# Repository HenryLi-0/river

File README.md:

<div align="center">
    <h2>River</h2>
    <p>by <a href= "https://github.com/HenryLi-0/river"> @HenryLi-0 </a></p>
    
</div>

<sub>All designs are open source! Hardware licensed under CERN OHL S v2.<sub>

# River

a quick stepping stone

---

## What this?

A couple of months ago, after listening to [archived](https://archive.org/details/the-sport-saver?webamp=default) [music](https://archive.org/details/under-the-ground?webamp=default) on the Internet Archive with Webamp, I thought the graphics on the right side (powered by Milkdrop) were pretty cool. I've always liked how Geometry Dash levels *typically* have well synced gameplay, since it's just so satisfying. Additionally, I also dislike how everything is switching to streamsing services (both because of the subscription model and more importantly the amount of cellular data it uses lol), so I basically wanted to bring music-synced graphics onto a portable offline device!

So, River is a relatively small PCB, hosting a dual RP2040 setup, each having custom firmware! The first one handles all the user controls, file loading, and the audio jack, while the second handles the display math, communicating with the first RP2040 by SPI and UART. Through this (rather unconventional) setup, audio can play continously while the second RP2040 works on more taxing graphics using the Pico SDK for C, with the second RP2040 basically just doing the graphics. It does this by having a PCM5101A and a TPA6132A2RTE into a TRS audio jack!

In retrospect, this project wasn't exactly a quick stepping stone (as in, it took over fifty hours of development), but it sure did review many topics surrounding PCB design with KiCAD, building on to what I learned from Hackpad and Raven! Originally, this was in case [fermion](http://github.com/HenryLi-0/fermion) would require a custom PCB, but who knows if it'll need one in the end. Anyways, working on River did teach a lot, as well as letting me have fun creating art for it!

---

Huge thanks to [this](https://blueprint.hackclub.com/starter-projects/devboard) guide from Blueprint and [this](https://pip-assets.raspberrypi.com/categories/814-rp2040/documents/RP-008279-DS-1-hardware-design-with-rp2040.pdf) documentation from Raspberry Pi for valuable information on RP2040 wiring design. Thanks!

---

## Pictures!

---

## Directory

- [CAD](</cad/README.md>)
    - The case is made in Onshape!
- [Firmware](</firmware/README.md>)
    - Two firmwares for the two RP2040s!
- [Updatelogs](</updatelogs/>)
    - As always, lots of behind the scenes content! It's also a decently long read as always :D
- [BOM](</BOM.csv>)
    - Want to build one yourself? Here's the BOM in CSV form! However, I suggest using the Google Sheets one, check down below for that!

---

## Usage

Assembly
1. First, one must obtain the PCB! It's not really made for hand-soldering, more so for JLCPCB's or any other PCBA service to assemble (but feel free to give it a try if super experienced!).
2. The main PCB's here? Great! Flash the two RP2040s with their specific firmwares and make sure all status LEDs and storage works! (Same process as testing a devboard, except there's not really any free pins...)
3. Once the RP2040s are confirmed to be in good condition, test the micro SD card slot and the audio jack! A micro SD card and a TRS audio plug (usually in random earbuds) are needed! Load music on and see if it works (after setting the firmware to play a song from the micro SD card).
4. Once those also work, solder on the displays and keys! This should be fairly straightforward, watch a soldering tutorial if needed! (Yes, a soldering iron is also needed!)
5. Assemble everything into the case and screw in the M2 screws! Adjust the case if needed if the audio plug doesn't fit well with the current slot!

---

## BOM

Note: This list was made in mid-September 2026. Depending on a ton of factors, this price may change over time, so these prices may be different! Multiple parts are sourced by me (since I have a bunch of extra parts laying around), so it will likely cost a bit more. Currently, shipping and tax estimates are included (to NYC), check out the `updatelogs` whenever construction occurs to find the actual price it resulted in!

[Here's](https://docs.google.com/spreadsheets/d/1_4eaDKRTe7VvPdyKRilJCp6rfzp3SGLLEaJtn6RHo0M/edit?gid=0#gid=0) the original Google Sheets BOM, color coded too! (It'll also be more updated, but I'll try to sync this one too!)

| Part                                      | Price         | Link          |
|-------------------------------------------|---------------|---------------|
| Board PCB (PCBA)                          | $84.61        | JLCPCB        |
| M2 Screws (16mm, 50pcs)                   | $1.41         | [AliExpress](https://www.aliexpress.us/item/3256804341271555.html) |
| 128x32 OLED Display (White, 1pc)          | $2.44         | [AliExpress](https://www.aliexpress.us/item/3256808453793642.html) |
| 128x160 TFT Display (1.8 inch TFT)        | $4.06         | [AliExpress](https://www.aliexpress.us/item/3256807859088652.html) |
| WS2812B LEDs (3)                          | $0.00         | Anywhere      |
| Micro SD Card (1)                         | $0.00         | Anywhere      |
| EC11 Rotary Encoder (1)                   | $0.00         | Anywhere      |
| Cherry MX Switch (3)                      | $0.00         | Anywhere      |
| Estimated Shipping (JLCPCB to NYC)        | $11.05        | JLCPCB        |
| Estimated Shipping (AliExpress to NYC)    | $0.00         | AliExpress    |
| Buffer                                    | $5.00         |               |
| TOTAL                                     | $108.57       |               |

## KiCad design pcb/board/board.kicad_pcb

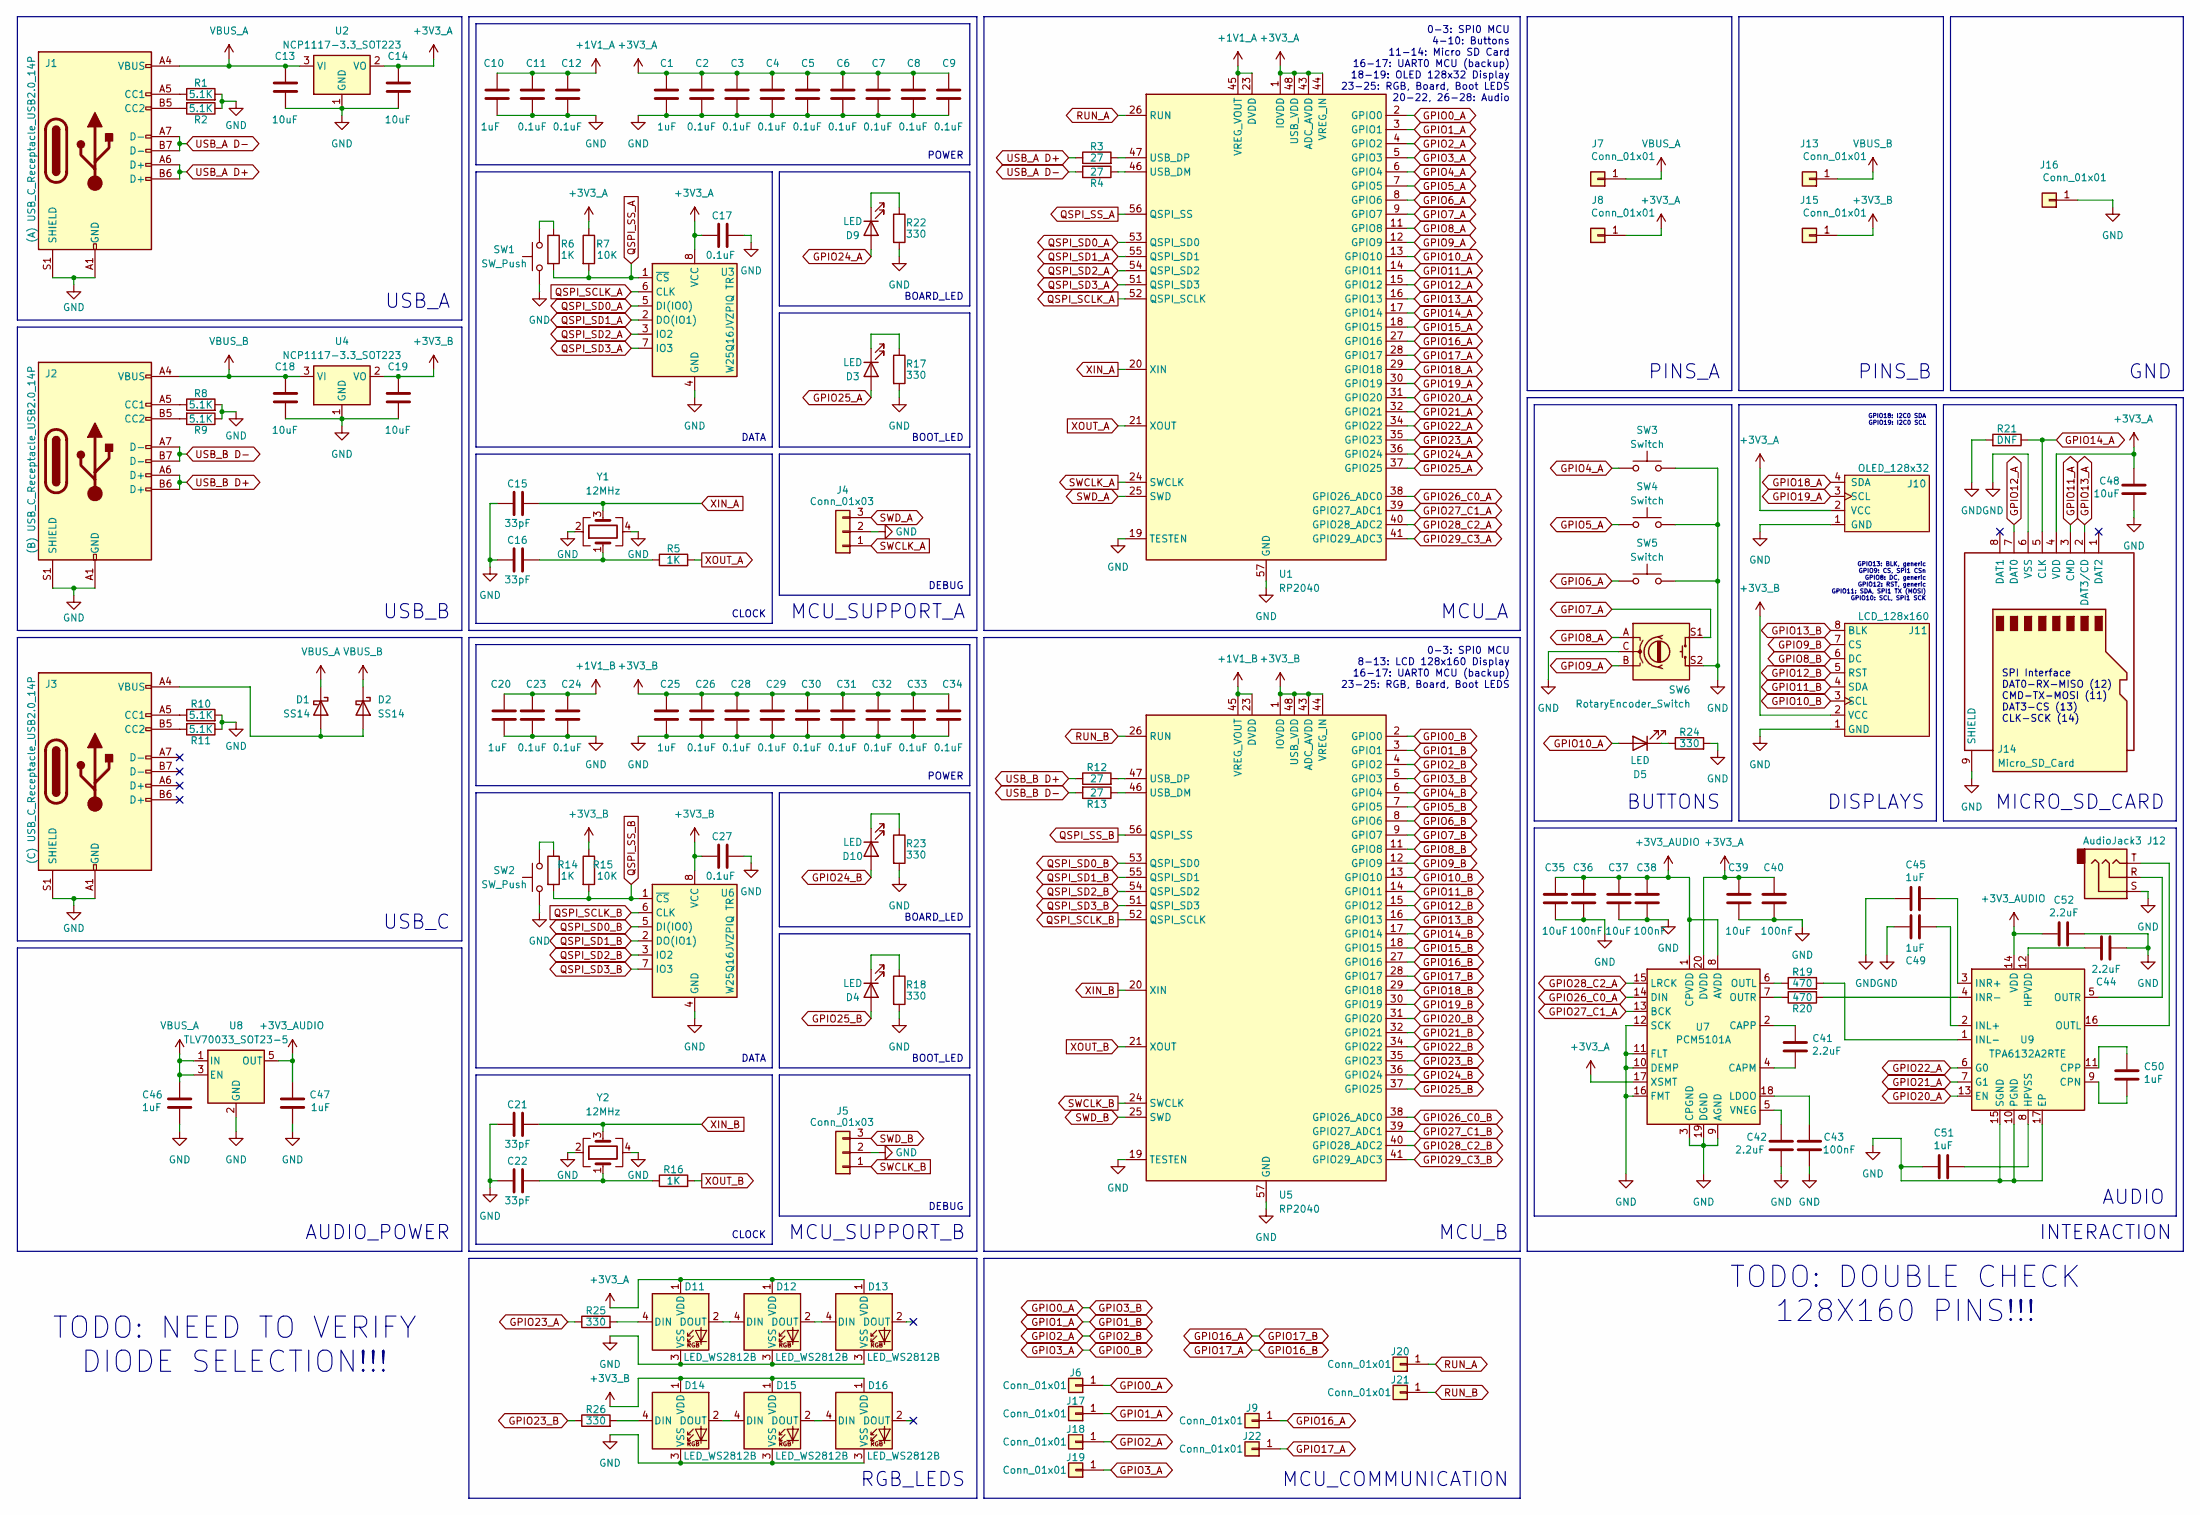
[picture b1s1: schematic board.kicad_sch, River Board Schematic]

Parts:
C1, C10, C20, C25, C45, C46, C47, C49, C50, C51: 1uF; C_0402_1005Metric
C2, C3, C4, C5, C6, C7, C8, C9, C11, C12, C17, C23, C24, C26, C27, C28, C29, C30, C31, C32, C33, C34: 0.1uF; C_0402_1005Metric
C13, C14, C18, C19: 10uF; C_0603_1608Metric
C15, C16, C21, C22: 33pF; C_0402_1005Metric
C35, C37, C39, C48: 10uF; C_0402_1005Metric
C36, C38, C40, C43: 100nF; C_0402_1005Metric
C41, C42, C44, C52: 2.2uF; C_0402_1005Metric
D1, D2: SS14; D_SMA
D3, D4, D5, D9, D10: LED; LED_0603_1608Metric
D11, D12, D13, D14, D15, D16: LED_WS2812B
J1: (A) USB_C_Receptacle_USB2.0_14P; USB_C_Receptacle_HRO_TYPE-C-31-M-12
J2: (B) USB_C_Receptacle_USB2.0_14P; USB_C_Receptacle_HRO_TYPE-C-31-M-12
J3: (C) USB_C_Receptacle_USB2.0_14P; USB_C_Receptacle_HRO_TYPE-C-31-M-12
J4, J5: Conn_01x03; PinHeader_1x03_P2.54mm_Vertical
J6, J9, J17, J18, J19, J20, J21, J22: Conn_01x01; TestPoint_Pad_D1.0mm
J7, J13: Conn_01x01; TestPoint_Pad_1.0x1.0mm
J8, J15, J16: Conn_01x01; PinHeader_1x01_P2.54mm_Vertical
J10: OLED_128x32
J11: LCD_128x160
J12: AudioJack3; Jack_3.5mm_CUI_SJ-3523-SMT_Horizontal
J14: Micro_SD_Card; microSD_HC_Molex_47219-2001
R1, R2, R8, R9, R10, R11: 5.1K; R_0402_1005Metric
R3, R4, R12, R13: 27; R_0402_1005Metric
R5, R6, R14, R16: 1K; R_0402_1005Metric
R7, R15: 10K; R_0402_1005Metric
R17, R18, R22, R23, R24, R25, R26: 330; R_0402_1005Metric
R19, R20: 470; R_0402_1005Metric
R21: DNF; R_0402_1005Metric
SW1, SW2: SW_Push; SW_Push_SPST_NO_Alps_SKRK
SW3, SW4, SW5: Switch; SW_Cherry_MX_1.00u_PCB
SW6: RotaryEncoder_Switch; RotaryEncoder_Alps_EC11E-Switch_Vertical_H20mm
U1, U5: RP2040; QFN-56-1EP_7x7mm_P0.4mm_EP3.2x3.2mm
U2, U4: NCP1117-3.3_SOT223; SOT-223-3_TabPin2
U3, U6: W25Q16JVZPIQ TR; Winbond_USON-8-1EP_3x2mm_P0.5mm_EP0.2x1.6mm
U7: PCM5101A; TSSOP-20_4.4x6.5mm_P0.65mm
U8: TLV70033_SOT23-5; SOT-23-5
U9: TPA6132A2RTE; WQFN-16-1EP_3x3mm_P0.5mm_EP1.6x1.6mm_ThermalVias
Y1, Y2: 12MHz; Crystal_SMD_3225-4Pin_3.2x2.5mm

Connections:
+1V1_A: C10.1, C11.1, C12.1, U1.23 (DVDD), U1.45 (VREG_VOUT), U1.50 (DVDD)
+1V1_B: C20.1, C23.1, C24.1, U5.23 (DVDD), U5.45 (VREG_VOUT), U5.50 (DVDD)
+3V3_A: C1.1, C2.1, C3.1, C4.1, C5.1, C6.1, C7.1, C8.1, C9.1, C14.1, C17.1, C39.1, C40.1, C48.1, D11.1 (VDD), D12.1 (VDD), D13.1 (VDD), J8.1, J10.2 (VCC), J14.4 (VDD), R7.1, U1.1 (IOVDD), U1.10 (IOVDD), U1.22 (IOVDD), U1.33 (IOVDD), U1.42 (IOVDD), U1.43 (ADC_AVDD), U1.44 (VREG_IN), U1.48 (USB_VDD), U1.49 (IOVDD), U2.2 (VO), U3.8 (VCC), U7.17 (XSMT), U7.20 (DVDD)
+3V3_AUDIO: C35.1, C36.1, C37.1, C38.1, C47.1, C52.1, U7.1 (CPVDD), U7.8 (AVDD), U8.5 (OUT), U9.14 (VDD)
+3V3_B: C19.1, C25.1, C26.1, C27.1, C28.1, C29.1, C30.1, C31.1, C32.1, C33.1, C34.1, D14.1 (VDD), D15.1 (VDD), D16.1 (VDD), J11.2 (VCC), J15.1, R15.1, U4.2 (VO), U5.1 (IOVDD), U5.10 (IOVDD), U5.22 (IOVDD), U5.33 (IOVDD), U5.42 (IOVDD), U5.43 (ADC_AVDD), U5.44 (VREG_IN), U5.48 (USB_VDD), U5.49 (IOVDD), U6.8 (VCC)
GND: C1.2, C2.2, C3.2, C4.2, C5.2, C6.2, C7.2, C8.2, C9.2, C10.2, C11.2, C12.2, C13.2, C14.2, C15.1, C16.1, C17.2, C18.2, C19.2, C20.2, C21.1, C22.1, C23.2, C24.2, C25.2, C26.2, C27.2, C28.2, C29.2, C30.2, C31.2, C32.2, C33.2, C34.2, C35.2, C36.2, C37.2, C38.2, C39.2, C40.2, C42.2, C43.2, C44.2, C45.1, C46.2, C47.2, C48.2, C49.1, C51.1, C52.2, D11.3 (VSS), D12.3 (VSS), D13.3 (VSS), D14.3 (VSS), D15.3 (VSS), D16.3 (VSS), J1.A1 (GND), J1.A12 (GND), J1.B1 (GND), J1.B12 (GND), J1.S1 (SHIELD), J2.A1 (GND), J2.A12 (GND), J2.B1 (GND), J2.B12 (GND), J2.S1 (SHIELD), J3.A1 (GND), J3.A12 (GND), J3.B1 (GND), J3.B12 (GND), J3.S1 (SHIELD), J4.2, J5.2, J10.1 (GND), J11.1 (GND), J12.S, J14.6 (VSS), J14.9 (SHIELD), J16.1, R1.2, R2.1, R8.2, R9.1, R10.2, R11.1, R17.2, R18.2, R21.2, R22.2, R23.2, R24.2, SW1.1, SW2.1, SW3.2, SW4.2, SW5.2, SW6.C, SW6.S2, U1.19 (TESTEN), U1.57 (GND), U2.1 (GND), U3.4 (GND), U4.1 (GND), U5.19 (TESTEN), U5.57 (GND), U6.4 (GND), U7.3 (CPGND), U7.9 (AGND), U7.10 (DEMP), U7.11 (FLT), U7.12 (SCK), U7.16 (FMT), U7.19 (DGND), U8.2 (GND), U9.10 (PGND), U9.15 (SGND), U9.17 (EP), Y1.2, Y1.4, Y2.2, Y2.4
GPIO0_A: J6.1, U1.2 (GPIO0), U5.5 (GPIO3)
GPIO0_B: J19.1, U1.5 (GPIO3), U5.2 (GPIO0)
GPIO1_A: J17.1, U1.3 (GPIO1), U5.3 (GPIO1)
GPIO2_A: J18.1, U1.4 (GPIO2), U5.4 (GPIO2)
GPIO4_A: SW3.1, U1.6 (GPIO4)
GPIO4_B: U5.6 (GPIO4)
GPIO5_A: SW4.1, U1.7 (GPIO5)
GPIO5_B: U5.7 (GPIO5)
GPIO6_A: SW5.1, U1.8 (GPIO6)
GPIO6_B: U5.8 (GPIO6)
GPIO7_A: SW6.S1, U1.9 (GPIO7)
GPIO7_B: U5.9 (GPIO7)
GPIO8_A: SW6.A, U1.11 (GPIO8)
GPIO8_B: J11.6 (DC), U5.11 (GPIO8)
GPIO9_A: SW6.B, U1.12 (GPIO9)
GPIO9_B: J11.7 (CS), U5.12 (GPIO9)
GPIO10_A: D5.2 (A), U1.13 (GPIO10)
GPIO10_B: J11.3 (SCL), U5.13 (GPIO10)
GPIO11_A: J14.3 (CMD), U1.14 (GPIO11)
GPIO11_B: J11.4 (SDA), U5.14 (GPIO11)
GPIO12_A: J14.7 (DAT0), U1.15 (GPIO12)
GPIO12_B: J11.5 (RST), U5.15 (GPIO12)
GPIO13_A: J14.2 (DAT3/CD), U1.16 (GPIO13)
GPIO13_B: J11.8 (BLK), U5.16 (GPIO13)
GPIO14_A: J14.5 (CLK), R21.1, U1.17 (GPIO14)
GPIO14_B: U5.17 (GPIO14)
GPIO15_A: U1.18 (GPIO15)
GPIO15_B: U5.18 (GPIO15)
GPIO16_A: J9.1, U1.27 (GPIO16), U5.28 (GPIO17)
GPIO16_B: J22.1, U1.28 (GPIO17), U5.27 (GPIO16)
GPIO18_A: J10.4 (SDA), U1.29 (GPIO18)
GPIO18_B: U5.29 (GPIO18)
GPIO19_A: J10.3 (SCL), U1.30 (GPIO19)
GPIO19_B: U5.30 (GPIO19)
GPIO20_A: U1.31 (GPIO20), U9.13 (EN)
GPIO20_B: U5.31 (GPIO20)
GPIO21_A: U1.32 (GPIO21), U9.7 (G1)
GPIO21_B: U5.32 (GPIO21)
GPIO22_A: U1.34 (GPIO22), U9.6 (G0)
GPIO22_B: U5.34 (GPIO22)
GPIO23_A: R25.1, U1.35 (GPIO23)
GPIO23_B: R26.1, U5.35 (GPIO23)
GPIO24_A: D9.2 (A), U1.36 (GPIO24)
GPIO24_B: D10.2 (A), U5.36 (GPIO24)
GPIO25_A: D3.2 (A), U1.37 (GPIO25)
GPIO25_B: D4.2 (A), U5.37 (GPIO25)
GPIO26_C0_A: U1.38 (GPIO26_ADC0), U7.14 (DIN)
GPIO26_C0_B: U5.38 (GPIO26_ADC0)
GPIO27_C1_A: U1.39 (GPIO27_ADC1), U7.13 (BCK)
GPIO27_C1_B: U5.39 (GPIO27_ADC1)
GPIO28_C2_A: U1.40 (GPIO28_ADC2), U7.15 (LRCK)
GPIO28_C2_B: U5.40 (GPIO28_ADC2)
GPIO29_C3_A: U1.41 (GPIO29_ADC3)
GPIO29_C3_B: U5.41 (GPIO29_ADC3)
unnamed: C16.2, R5.1, Y1.1
unnamed: C22.2, R16.1, Y2.1
unnamed: D1.2 (A), D2.2 (A), J3.A4 (VBUS), J3.A9 (VBUS), J3.B4 (VBUS), J3.B9 (VBUS)
unnamed: D3.1 (K), R17.1
unnamed: D4.1 (K), R18.1
unnamed: D5.1 (K), R24.1
unnamed: D9.1 (K), R22.1
unnamed: D10.1 (K), R23.1
unnamed: D11.4 (DIN), R25.2
unnamed: D11.2 (DOUT), D12.4 (DIN)
unnamed: D12.2 (DOUT), D13.4 (DIN)
unnamed: D14.4 (DIN), R26.2
unnamed: D14.2 (DOUT), D15.4 (DIN)
unnamed: D15.2 (DOUT), D16.4 (DIN)
unnamed: J1.A5 (CC1), R1.1
unnamed: J1.B5 (CC2), R2.2
unnamed: J2.A5 (CC1), R8.1
unnamed: J2.B5 (CC2), R9.2
unnamed: J3.A5 (CC1), R10.1
unnamed: J3.B5 (CC2), R11.2
unnamed: R6.1, SW1.2
unnamed: R14.1, SW2.2
unnamed: R4.1, U1.46 (USB_DM)
unnamed: R3.2, U1.47 (USB_DP)
unnamed: R13.1, U5.46 (USB_DM)
unnamed: R12.2, U5.47 (USB_DP)
unnamed: C41.2, U7.4 (CAPM)
unnamed: C41.1, U7.2 (CAPP)
unnamed: C43.1, U7.18 (LDOO)
unnamed: R19.1, U7.6 (OUTL)
unnamed: R20.1, U7.7 (OUTR)
unnamed: C42.1, U7.5 (VNEG)
unnamed: C50.2, U9.9 (CPN)
unnamed: C50.1, U9.11 (CPP)
unnamed: C44.1, U9.12 (HPVDD)
unnamed: C51.2, U9.8 (HPVSS)
unnamed: C49.2, U9.2 (INL+)
unnamed: R19.2, U9.1 (INL-)
unnamed: C45.2, U9.3 (INR+)
unnamed: R20.2, U9.4 (INR-)
unnamed: J12.T, U9.16 (OUTL)
unnamed: J12.R, U9.5 (OUTR)
QSPI_SCLK_A: U1.52 (QSPI_SCLK), U3.6 (CLK)
QSPI_SCLK_B: U5.52 (QSPI_SCLK), U6.6 (CLK)
QSPI_SD0_A: U1.53 (QSPI_SD0), U3.5 (DI(IO0))
QSPI_SD0_B: U5.53 (QSPI_SD0), U6.5 (DI(IO0))
QSPI_SD1_A: U1.55 (QSPI_SD1), U3.2 (DO(IO1))
QSPI_SD1_B: U5.55 (QSPI_SD1), U6.2 (DO(IO1))
QSPI_SD2_A: U1.54 (QSPI_SD2), U3.3 (IO2)
QSPI_SD2_B: U5.54 (QSPI_SD2), U6.3 (IO2)
QSPI_SD3_A: U1.51 (QSPI_SD3), U3.7 (IO3)
QSPI_SD3_B: U5.51 (QSPI_SD3), U6.7 (IO3)
QSPI_SS_A: R6.2, R7.2, U1.56 (QSPI_SS), U3.1 (~CS)
QSPI_SS_B: R14.2, R15.2, U5.56 (QSPI_SS), U6.1 (~CS)
RUN_A: J20.1, U1.26 (RUN)
RUN_B: J21.1, U5.26 (RUN)
SWCLK_A: J4.1, U1.24 (SWCLK)
SWCLK_B: J5.1, U5.24 (SWCLK)
SWD_A: J4.3, U1.25 (SWD)
SWD_B: J5.3, U5.25 (SWD)
USB_A D+: J1.A6 (D+), J1.B6 (D+), R3.1
USB_A D-: J1.A7 (D-), J1.B7 (D-), R4.2
USB_B D+: J2.A6 (D+), J2.B6 (D+), R12.1
USB_B D-: J2.A7 (D-), J2.B7 (D-), R13.2
VBUS_A: C13.1, C46.1, D1.1 (K), J1.A4 (VBUS), J1.A9 (VBUS), J1.B4 (VBUS), J1.B9 (VBUS), J7.1, U2.3 (VI), U8.1 (IN), U8.3 (EN)
VBUS_B: C18.1, D2.1 (K), J2.A4 (VBUS), J2.A9 (VBUS), J2.B4 (VBUS), J2.B9 (VBUS), J13.1, U4.3 (VI)
XIN_A: C15.2, U1.20 (XIN), Y1.3
XIN_B: C21.2, U5.20 (XIN), Y2.3
XOUT_A: R5.2, U1.21 (XOUT)
XOUT_B: R16.2, U5.21 (XOUT)

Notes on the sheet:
MICRO_SD_CARD
MCU_SUPPORT_A
PINS_B
CLOCK
BOOT_LED
BUTTONS
RGB_LEDS
DATA
AUDIO
USB_C
POWER
USB_B
MCU_A
MCU_B
DEBUG
INTERACTION
MCU_SUPPORT_B
BOARD_LED
USB_A
DISPLAYS
PINS_A
GND
MCU_COMMUNICATION
AUDIO_POWER
GPIO13: BLK, generic GPIO9: CS, SPI1 CSn GPIO8: DC, generic GPIO12: RST, generic GPIO11: SDA, SPI1 TX (MOSI) GPIO10: SCL, SPI1 SCK
0-3: SPI0 MCU 4-10: Buttons 11-14: Micro SD Card 16-17: UART0 MCU (backup) 18-19: OLED 128x32 Display 23-25: RGB, Board, Boot LEDS 20-22, 26-28: Audio
0-3: SPI0 MCU 8-13: LCD 128x160 Display 16-17: UART0 MCU (backup) 23-25: RGB, Board, Boot LEDS
GPIO18: I2C0 SDA GPIO19: I2C0 SCL
TODO: NEED TO VERIFY DIODE SELECTION!!!
TODO: DOUBLE CHECK 128X160 PINS!!!
SPI Interface DAT0-RX-MISO (12) CMD-TX-MOSI (11) DAT3-CS (13) CLK-SCK (14)

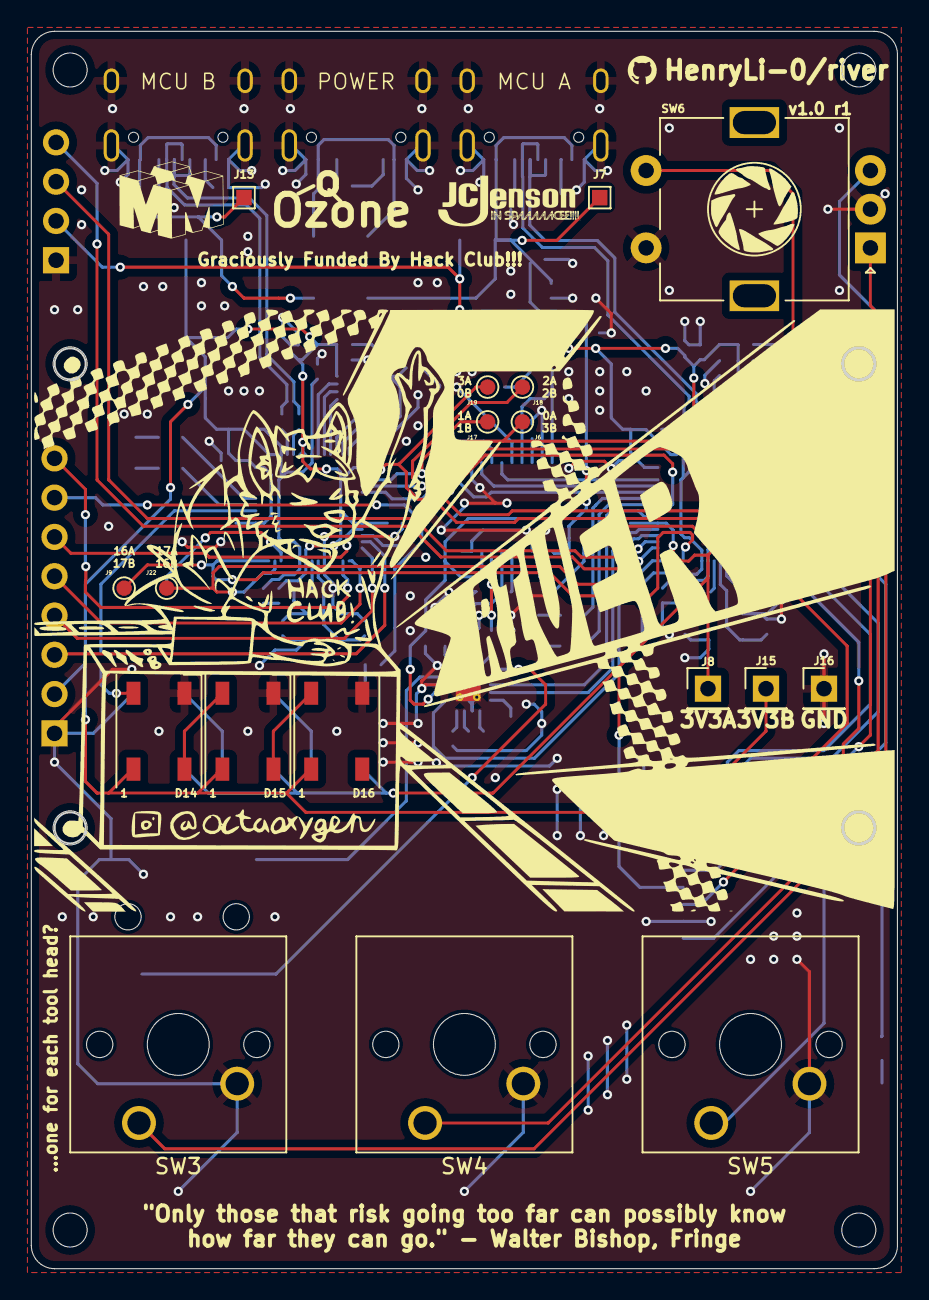
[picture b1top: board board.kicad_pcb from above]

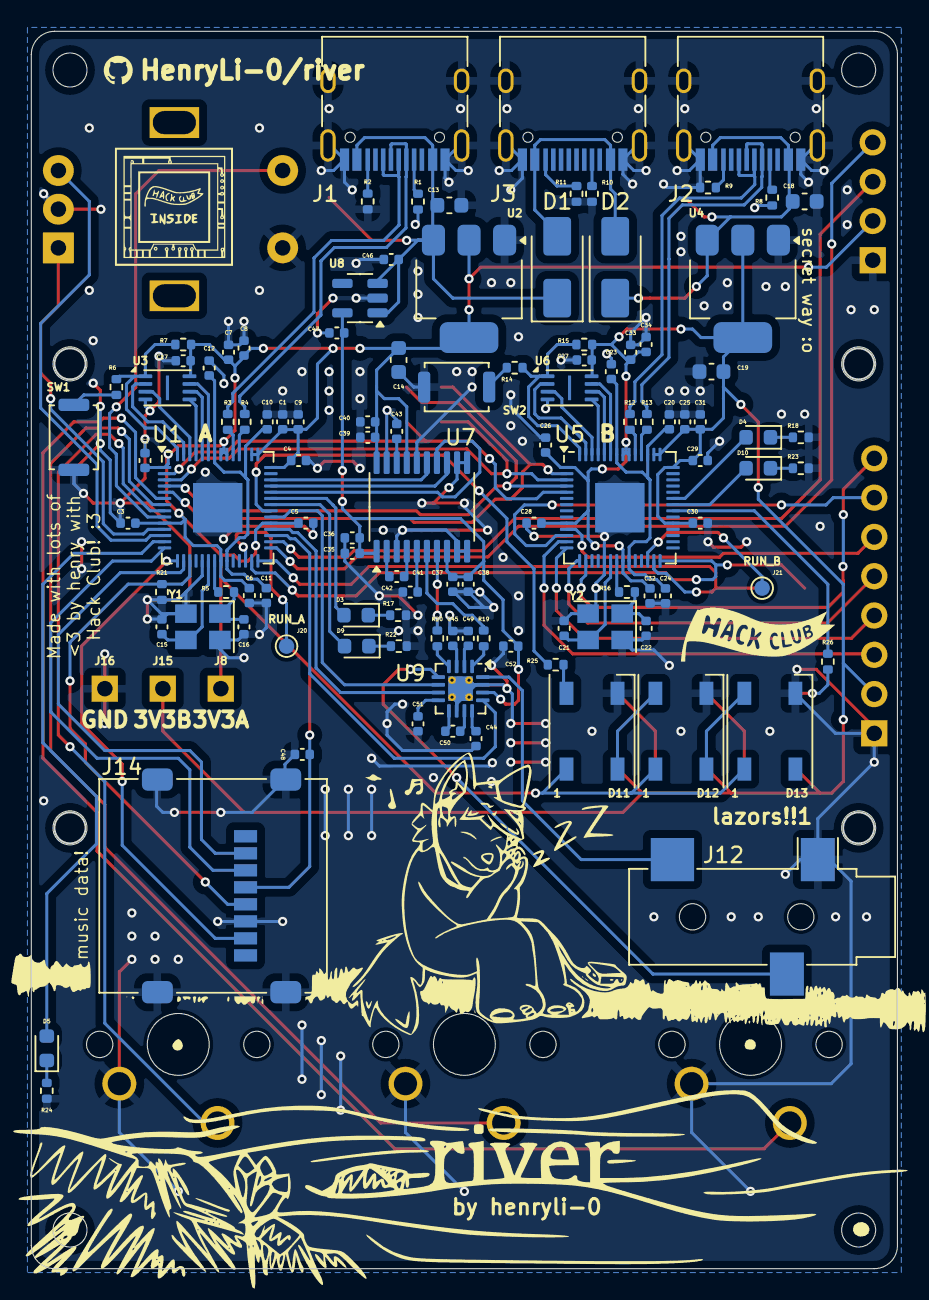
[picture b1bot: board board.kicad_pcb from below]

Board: 2 copper layers, 56.0 x 80.0 mm, 128 parts (108 on the bottom side), 109 nets.
